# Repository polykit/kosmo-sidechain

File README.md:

# Kosmo Sidechain (Ducking) Module

This repository contains schematics and PCB layout files of a Sidechain/Ducking module in Kosmo format originating on a design by Juanito Moore. Gerber files can be found in the [plots](plots/) directory.

## Schematics & PCB

## BOM

|Ref           |Qnty|Value     |Name               |Description                                                     |
|--------------|----|----------|-------------------|----------------------------------------------------------------|
|C1            |1   |1u        |CP-Device          |Polarized capacitor                                             |
|C2, C3        |2   |10u       |CP-Device          |Polarized capacitor                                             |
|C4            |1   |100n      |C                  |Unpolarized capacitor                                           |
|D1, D2, D3, D4|4   |1N4148    |1N4148             |100V 0.15A standard switching diode, DO-35                      |
|J1            |1   |Kick      |AudioJack2         |Audio Jack, Mono, 6,35mm                                        |
|J2            |1   |In        |AudioJack2         |Audio Jack, Mono, 6,35mm                                        |
|J3            |1   |Out       |AudioJack2         |Audio Jack, Mono, 6,35mm                                        |
|J4            |1   |POWER     |Conn_02x05_Odd_Even|10-pin IDC Connector                                            |
|R1            |1   |10k       |R                  |Resistor                                                        |
|R2, R8        |2   |100k      |R                  |Resistor                                                        |
|R3            |1   |33k       |R                  |Resistor                                                        |
|R4, R6        |2   |47k       |R                  |Resistor                                                        |
|R5, R9        |2   |220       |R                  |Resistor                                                        |
|R7            |1   |1k        |R                  |Resistor                                                        |
|R10, R11      |2   |10        |R                  |Resistor                                                        |
|RV1           |1   |Mix 10k   |R_POT-Device       |Potentiometer                                                   |
|RV2           |1   |Amount 10k|R_POT-Device       |Potentiometer                                                   |
|RV3           |1   |Decay 100k|R_POT-Device       |Potentiometer                                                   |
|U1            |1   |TL074     |TL074              |Quad Low-Noise JFET-Input Operational Amplifiers, DIP-14/SOIC-14|
|U2            |1   |Vactrol   |VTL5C              |Low Cost Axial Vactrols                                         |

## References

https://www.youtube.com/watch?v=cXaip9cjlhU

https://www.instructables.com/Freestyle-High-Fidelity-Ducking-Circuit/

https://lookmumnocomputer.discourse.group/t/side-chain-module-ducking

https://www.lookmumnocomputer.com/modular

https://github.com/telec16/kicad

https://github.com/holmesrichards/Kosmo_panel

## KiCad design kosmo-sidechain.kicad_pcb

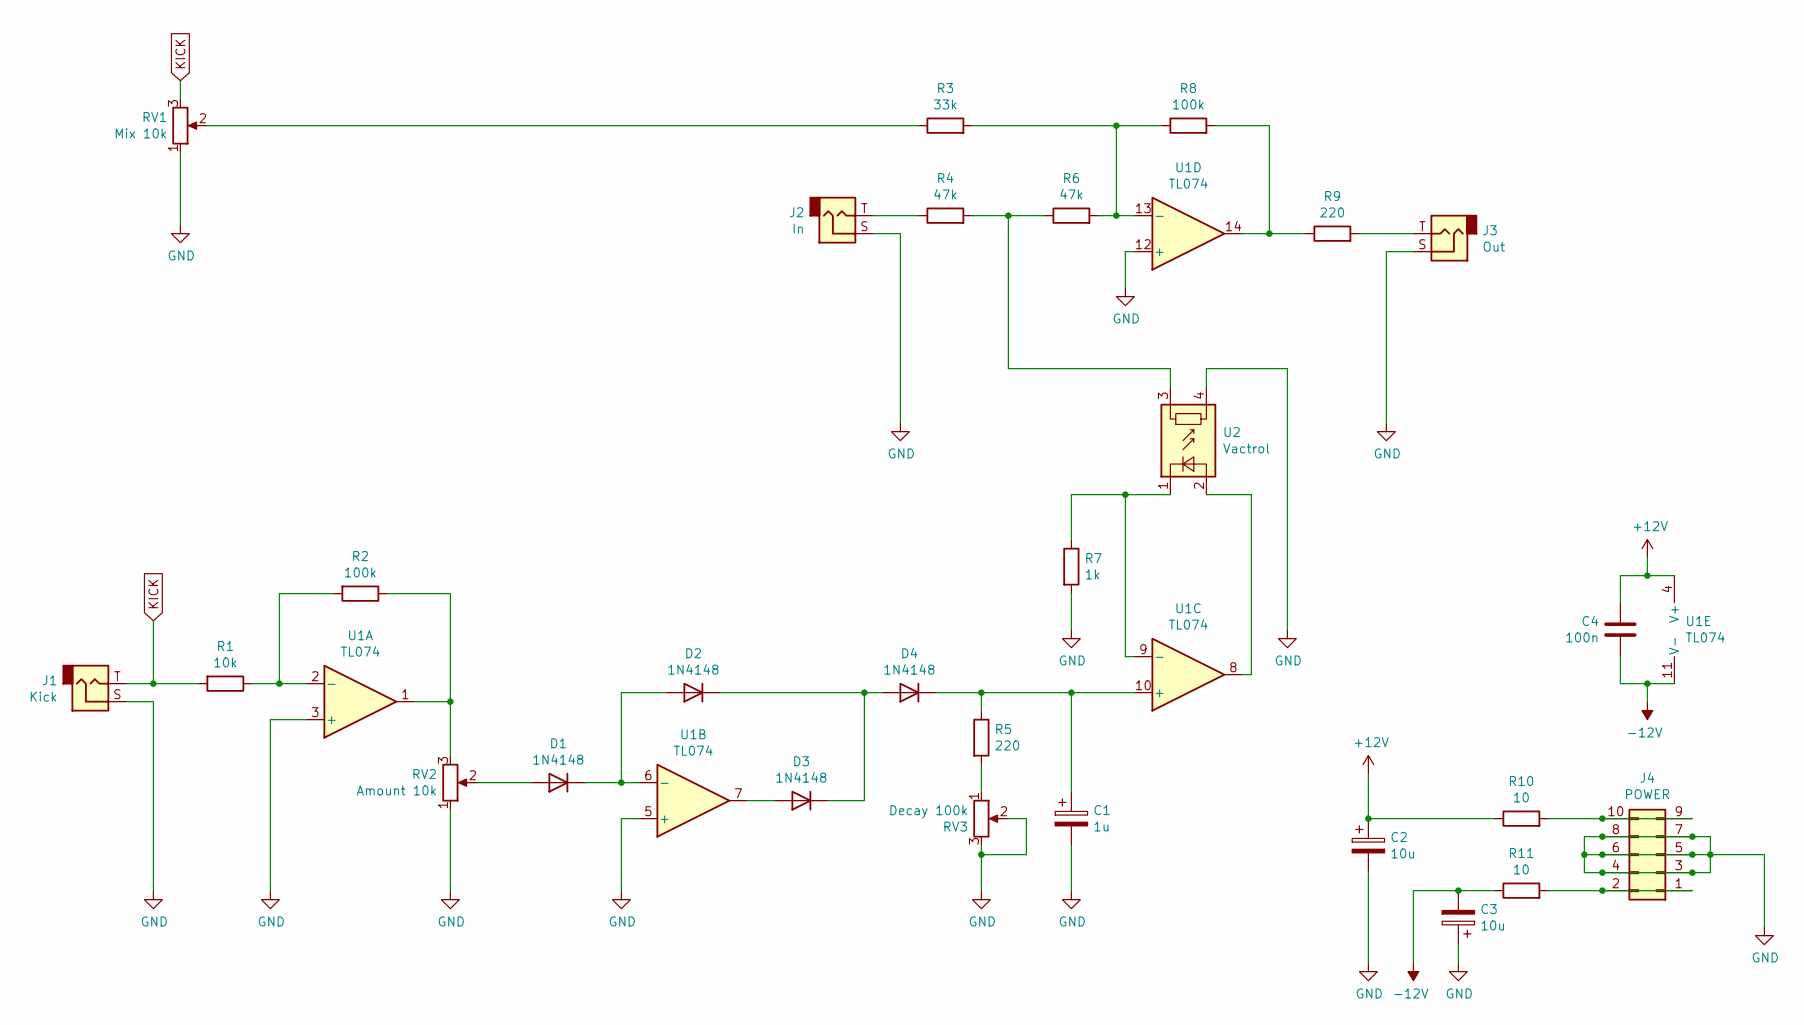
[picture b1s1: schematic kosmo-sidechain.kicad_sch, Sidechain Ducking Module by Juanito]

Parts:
C1: 1u; CP_Radial_D5.0mm_P2.00mm
C2, C3: 10u; CP_Radial_D5.0mm_P2.00mm
C4: 100n; C_Disc_D3.8mm_W2.6mm_P2.50mm
D1, D2, D3, D4: 1N4148; D_DO-35_SOD27_P7.62mm_Horizontal
J1: Kick; Jack_Hole_Square
J2: In; Jack_Hole_Square
J3: Out; Jack_Hole_Square
J4: POWER; IDC-Header_2x05_P2.54mm_Vertical
R1: 10k; R_Axial_DIN0207_L6.3mm_D2.5mm_P10.16mm_Horizontal
R2, R8: 100k; R_Axial_DIN0207_L6.3mm_D2.5mm_P10.16mm_Horizontal
R3: 33k; R_Axial_DIN0207_L6.3mm_D2.5mm_P10.16mm_Horizontal
R4, R6: 47k; R_Axial_DIN0207_L6.3mm_D2.5mm_P10.16mm_Horizontal
R5, R9: 220; R_Axial_DIN0207_L6.3mm_D2.5mm_P10.16mm_Horizontal
R7: 1k; R_Axial_DIN0207_L6.3mm_D2.5mm_P10.16mm_Horizontal
R10, R11: 10; R_Axial_DIN0207_L6.3mm_D2.5mm_P10.16mm_Horizontal
RV1: Mix 10k; Potentiometer_Single_Vertical_Hole
RV2: Amount 10k; Potentiometer_Single_Vertical_Hole
RV3: Decay 100k; Potentiometer_Single_Vertical_Hole
U1: TL074; DIP-14_W7.62mm_Socket_LongPads
U2: Vactrol; PerkinElmer_VTL5C

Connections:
+12V: C2.1, C4.1, R10.1, U1.4 (V+)
-12V: C3.2, C4.2, R11.1, U1.11 (V-)
GND: C1.2, C2.2, C3.1, J1.S, J2.S, J3.S, J4.3, J4.4, J4.5, J4.6, J4.7, J4.8, R7.2, RV1.1, RV2.1, RV3.2, RV3.3, U1.3 (+), U1.5 (+), U1.12 (+), U2.4
KICK: J1.T, R1.2, RV1.3
unnamed: C1.1, D4.1 (K), R5.1, U1.10 (+)
unnamed: D1.1 (K), D2.2 (A), U1.6 (-)
unnamed: D1.2 (A), RV2.2
unnamed: D2.1 (K), D3.1 (K), D4.2 (A)
unnamed: D3.2 (A), U1.7
unnamed: J2.T, R4.1
unnamed: J3.T, R9.2
unnamed: J4.1, J4.2, R11.2
unnamed: J4.9, J4.10, R10.2
unnamed: R1.1, R2.2, U1.2 (-)
unnamed: R2.1, RV2.3, U1.1
unnamed: R3.1, RV1.2
unnamed: R3.2, R6.2, R8.1, U1.13 (-)
unnamed: R4.2, R6.1, U2.3
unnamed: R5.2, RV3.1
unnamed: R7.1, U1.9 (-), U2.1 (-)
unnamed: R8.2, R9.1, U1.14
unnamed: U1.8, U2.2 (+)

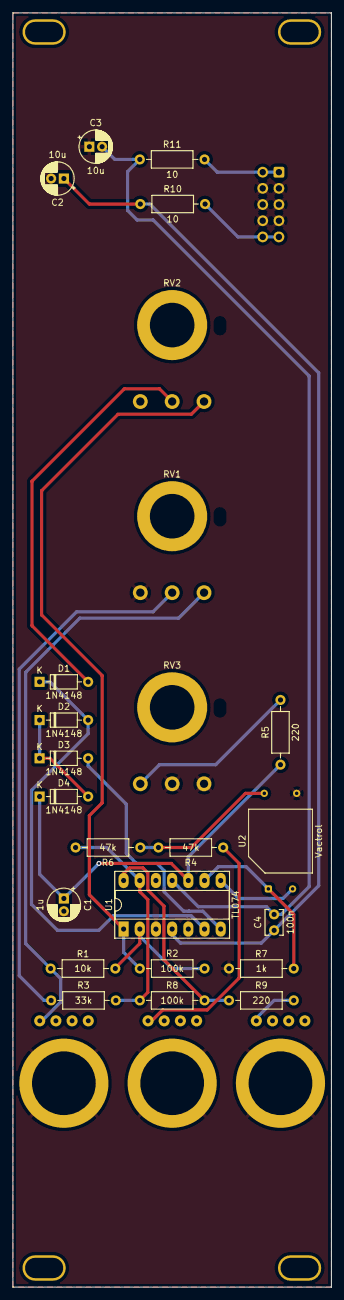
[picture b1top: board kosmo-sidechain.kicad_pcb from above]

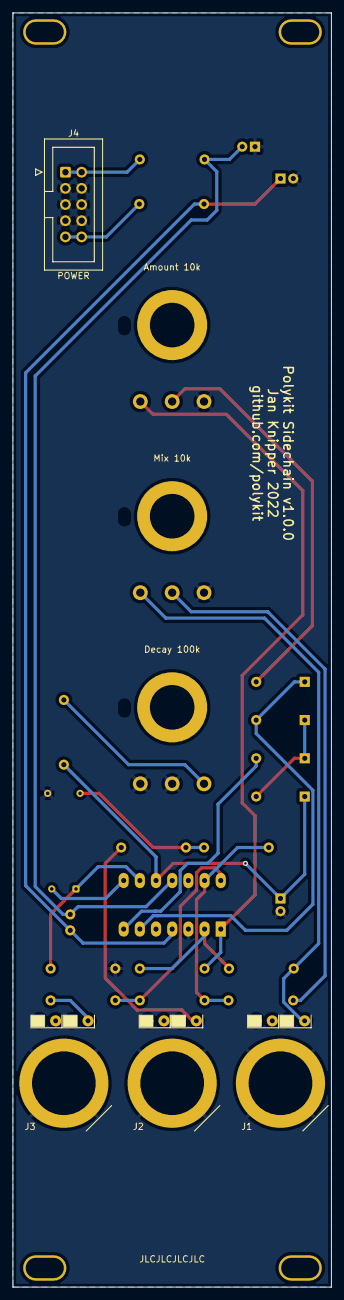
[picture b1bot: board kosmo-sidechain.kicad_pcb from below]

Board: 2 copper layers, 50.0 x 200.0 mm, 28 parts (4 on the bottom side), 22 nets.

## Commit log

2022-12-15 Initial import
2022-12-16 Changes readme
2022-12-17 Add more references
